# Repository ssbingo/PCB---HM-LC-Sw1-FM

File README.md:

# PCB und Gehäuse für HM-LC-Sw1-FM

## Bilder

## Schaltplan

[:arrow_right: Schaltplan](Images/HM-LC-Sw1-FM_Schaltplan.pdf)

## Platine

[:arrow_right: PCB Gerber](Platine/HM-LC-Sw1-FM_V2.zip)

## Gehäuse

<br>

<br>

<br>

<br>

<br>

<br>

<br>

<br>

## Aufbau / Stückliste

### Der Aufbau

fertig bestückte Platine <br>

fertig bestückte Platine <br>

### Die benötigten Bauteile
| Bauteil | Link |
| --------|------|
| | |

## Hinweise

- :exclamation:

## Lizenz

**Creative Commons BY-NC-SA**<br>
Give Credit, NonCommercial, ShareAlike

<br />This work is licensed under a <a rel="license" href="http://creativecommons.org/licenses/by-nc-sa/4.0/">Creative Commons Attribution-NonCommercial-ShareAlike 4.0 International License</a>.

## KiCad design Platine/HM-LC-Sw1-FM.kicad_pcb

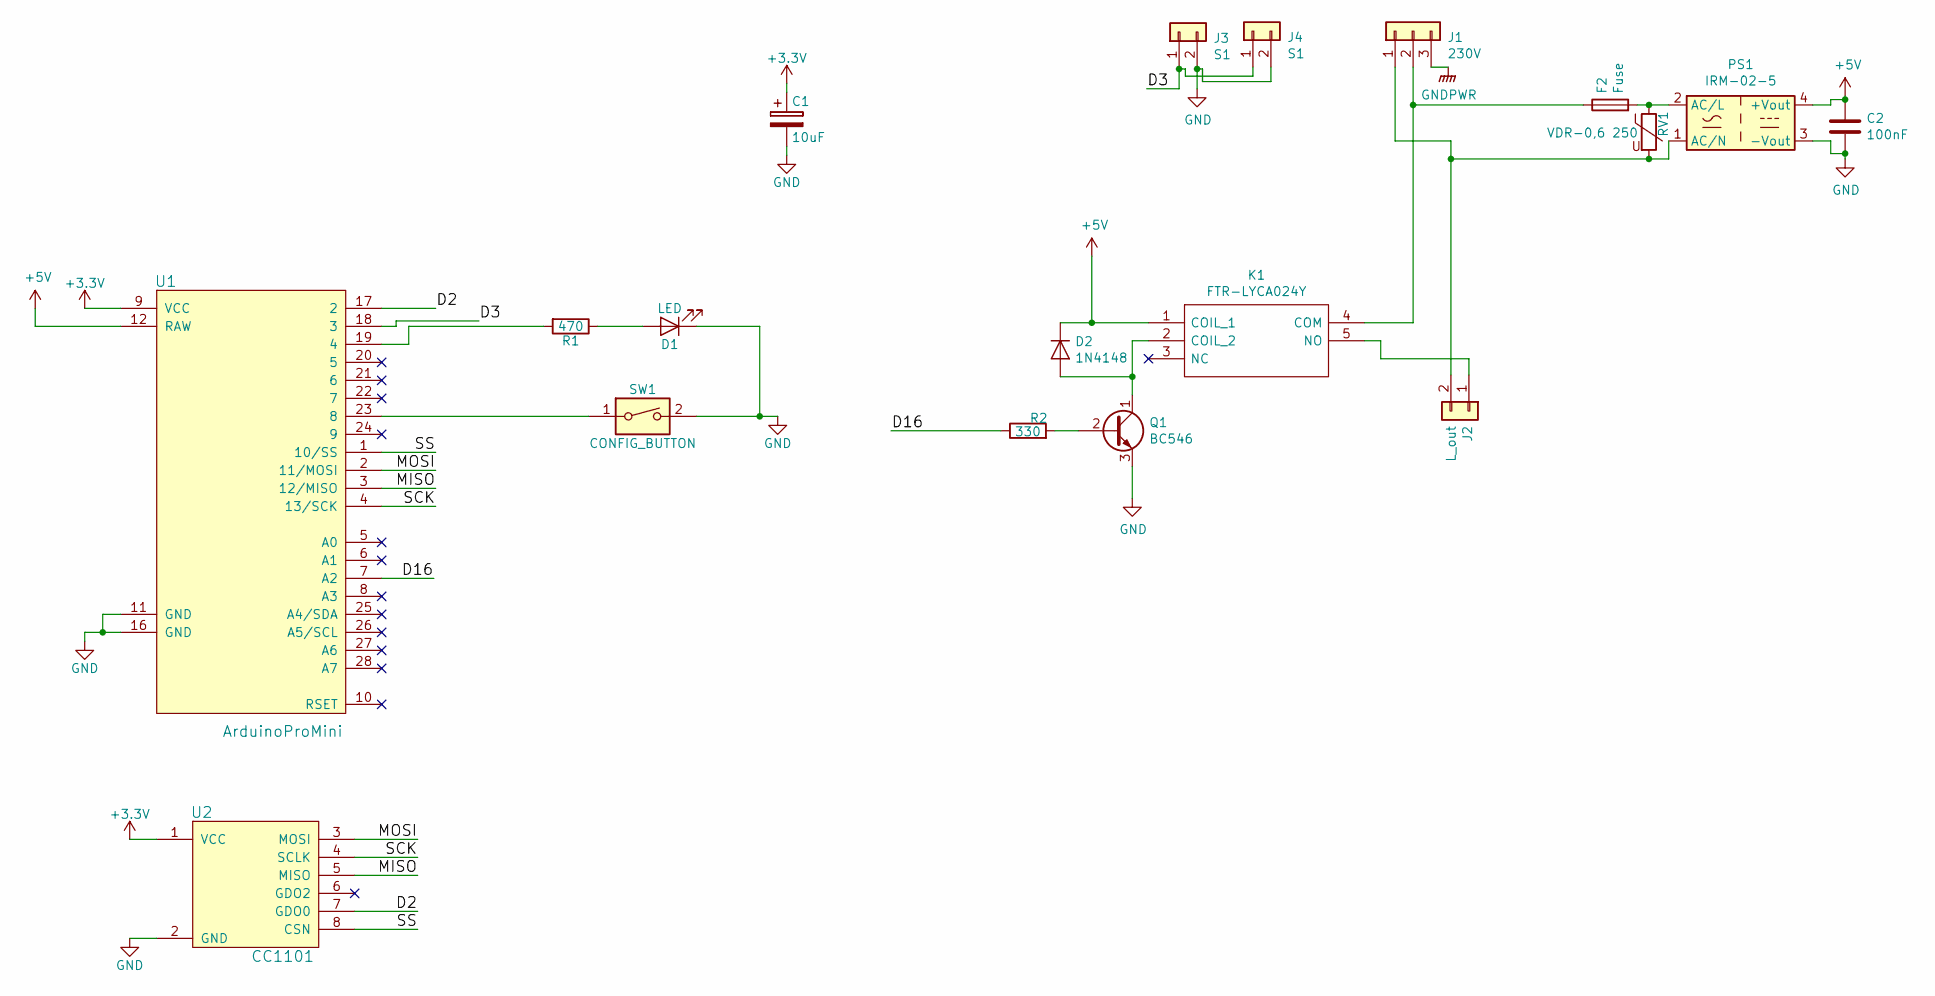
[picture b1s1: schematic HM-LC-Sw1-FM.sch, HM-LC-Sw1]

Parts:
C1: 10uF; CP_Radial_D4.0mm_P1.50mm
C2: 100nF; C_Disc_D5.0mm_W2.5mm_P2.50mm
D1: LED; LED_D3.0mm
D2: 1N4148; D_DO-35_SOD27_P7.62mm_Horizontal
F2: Fuse; Fuse_Schurter_318265
J1: 230V; TerminalBlock_WAGO_236-103_1x03_P5.00mm_45Degree
J2: L_out; TerminalBlock_WAGO_236-102_1x02_P5.00mm_45Degree
J3: S1; TerminalBlock_WAGO_236-102_1x02_P5.00mm_45Degree
J4: S1; PinHeader_1x02_P2.54mm_Vertical
K1: FTR-LYCA024Y; FTRLYCA024Y; Manufacturer_Part_Number FTR-LYCA024Y; Mouser Part Number 817-FTR-LYCA024Y
PS1: IRM-02-5; Converter_ACDC_MeanWell_IRM-05-xx_THT
Q1: BC546; TO-92_Inline
R1: 470; R_Axial_DIN0207_L6.3mm_D2.5mm_P2.54mm_Vertical
R2: 330; R_Axial_DIN0207_L6.3mm_D2.5mm_P2.54mm_Vertical
RV1: VDR-0,6 250; RV_Disc_D9mm_W5.7mm_P5mm
SW1: CONFIG_BUTTON; SW_PUSH_6mm_H5mm
U1: ArduinoProMini
U2: CC1101

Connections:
+3V3: C1.1, U1.9 (VCC), U2.1 (VCC)
+5V: C2.1, D2.1 (K), K1.1 (COIL_1), PS1.4 (+Vout), U1.12 (RAW)
/D2: U1.17 (2), U2.7 (GDO0)
/D3: J3.1, J4.1, U1.18 (3)
/D16: R2.1, U1.7 (A2)
/MISO: U1.3 (12/MISO), U2.5 (MISO)
/MOSI: U1.2 (11/MOSI), U2.3 (MOSI)
/SCK: U1.4 (13/SCK), U2.4 (SCLK)
/SS: U1.1 (10/SS), U2.8 (CSN)
GND: C1.2, C2.2, D1.1 (K), J3.2, J4.2, PS1.3 (-Vout), Q1.3 (E), SW1.2, U1.11 (GND), U1.16 (GND), U2.2 (GND)
GNDPWR: J1.3
unnamed: D1.2 (A), R1.1
unnamed: D2.2 (A), K1.2 (COIL_2), Q1.1 (C)
unnamed: F2.1, J1.2, K1.4 (COM)
unnamed: F2.2, PS1.2 (AC/L), RV1.1
unnamed: J1.1, J2.2, PS1.1 (AC/N), RV1.2
unnamed: J2.1, K1.5 (NO)
unnamed: Q1.2 (B), R2.2
unnamed: R1.2, U1.19 (4)
unnamed: SW1.1, U1.23 (8)

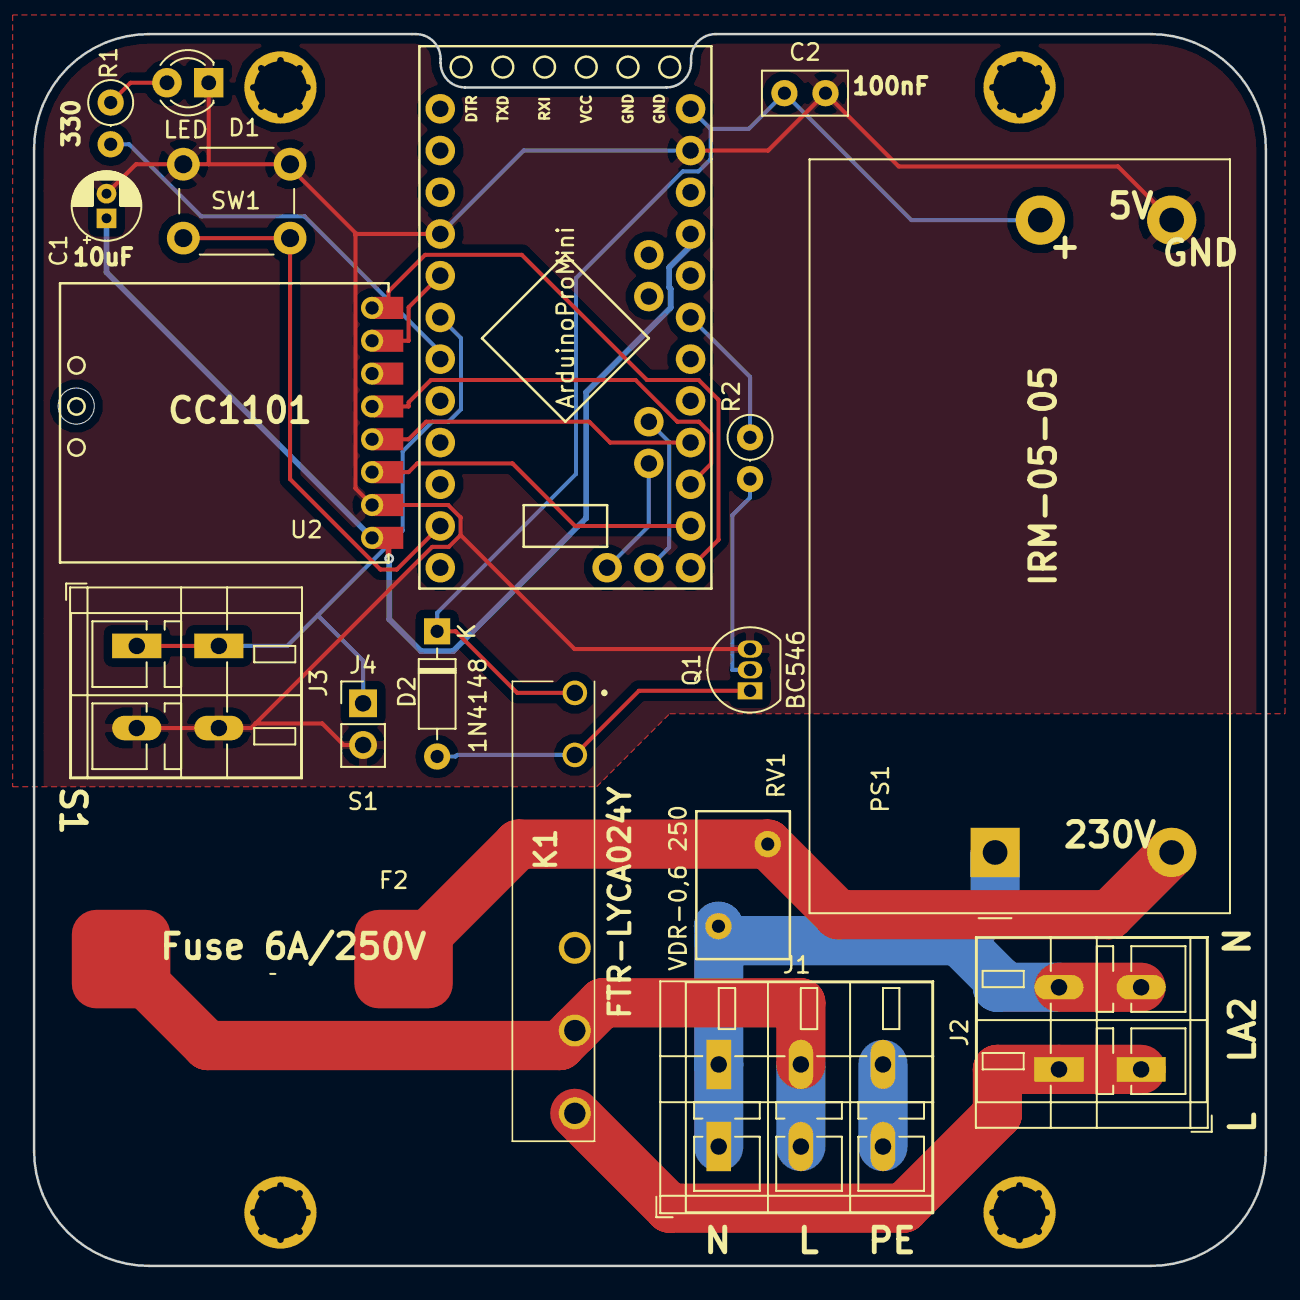
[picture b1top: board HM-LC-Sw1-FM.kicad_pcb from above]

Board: 2 copper layers, 75.0 x 75.0 mm, 24 parts (0 on the bottom side), 19 nets.

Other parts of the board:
Cp1: Version 2.0.1 - 02/2020; Copyrigth
P1: MountingHole_2.2mm_M2
P2, P3, P4, P5: MountingHole_2.2mm_M2_Pad_Via

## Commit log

2020-02-26 Images

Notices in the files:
Platine/HM-LC-Sw1-FM.kicad_pcb:
©S. Sternitzke
parts and their libraries:
© Silvio Sternitzke
